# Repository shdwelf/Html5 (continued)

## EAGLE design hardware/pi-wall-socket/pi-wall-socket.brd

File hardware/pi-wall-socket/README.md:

# Pi Wall Socket — a Raspberry Pi Zero 2 W carrier with Ethernet and powerline

Generated CAD: `node tools/build-wallplug-eagle.mjs --design=pi-wall-socket --check`
re-derives these files from `tools/pi-socket-model.mjs` and compares.

| file | what it is |
| --- | --- |
| `pi-wall-socket.lbr` | 22 packages, 18 symbols, 23 devicesets |
| `pi-wall-socket.sch` | 1 sheet (520 × 500 mm), 41 instances, 35 nets |
| `pi-wall-socket.brd` | 180 × 120 mm, 2 layers, 45 elements, 175 pads — **unrouted on purpose** |
| `BOM.md` | every reference, package, fit/DNP, zone, note |

## What it is

A carrier board for a **Raspberry Pi Zero 2 W** that is meant to live in a
wall-socket enclosure. It takes L/N/PE from the socket's own terminals, makes
isolated 12 V, then 5 V for the Pi and 3.3 V for everything else, and gives the Pi
the two network paths it does not have: **wired Ethernet** and
**Ethernet-over-powerline**.

```
L ── F1 ──┬── PS1 (MPM-20-12, 12 V) ──┬── U1 LM2576S-5.0 ── 5 V ── Pi header pins 2/4
          │                           └── U2 LM2576S-3.3 ── 3.3 V ─┬── U4 WIZ850io (SPI0)
N ────────┤                                                        └── U3 PLC Stamp mini 2 (SPI1)
          └── U3 pins 16/17 (L), 15 (N)   ← the modem couples onto the mains
PE ─── J1.3 only, never bonded to SELV ground
```

Why a Zero 2 W and not a Pi 4 or a CM4: the Zero 2 W is 65 × 30 mm with four M2.5
holes on 58 × 23 mm centres, so it fits behind a socket faceplate, and it has no
Ethernet — which is exactly the gap this carrier fills. It is a quad Cortex-A53
(RP3A0/BCM2710A1) at 1 GHz with 512 MB, 2.4 GHz Wi-Fi and BT 4.2, drawing about
3 W max. The industrial alternative is a Compute Module 4, which has an Ethernet
PHY on the module (pins 3-12 are `Ethernet_Pair0..3 P/N`) and takes 5 V on six
pins, but needs two 100-way 0.4 mm DF40C-100DS mezzanine connectors; the PIONIX
EVerest Yak is a published CM4 carrier of exactly that kind.

## Design rules

| rule | value | source |
| --- | --- | --- |
| mains ↔ SELV creepage | **8.0 mm** | PLC Stamp mini 2 datasheet rev 13 §8.3 |
| mains ↔ SELV clearance | 6.5 mm | same |
| isolation | 4000 Vac, inside U3 | same |
| Pi 5 V | header pins 2/4, ≈600 mA max | Pi Zero 2 W: ≈3 W at 5 V |
| Pi 3.3 V output | **left open** | pins 1/17 are the Pi's own regulator, ≈50 mA; paralleling it with a 3 A rail would be a mistake |

`--check` reports the worst mains↔SELV pair as **U3.15 ↔ U3.13 = 13.12 mm** — the
modem's own N pad against its own ZC_IN pad.

## Power budget

| rail | source | loads | margin |
| --- | --- | --- | --- |
| 12 V | MPM-20-12, 20 W | 5 V buck input 391 mA + 3.3 V buck input 206 mA = 597 mA | 64 % |
| 5 V | LM2576S-5.0, 3 A | Pi Zero 2 W 600 mA | 80 % |
| 3.3 V | LM2576S-3.3, 3 A | U3 300 mA (§8.2 max) + U4 180 mA + LEDs/straps/breakout 80 mA = 560 mA | 81 % |

Two buck regulators rather than one: the Pi wants 5 V and the modem wants 3.3 V at
up to 300 mA, and an LDO from 5 V at that current is 0.85 W of heat in a SOT-223.

## The Pi interface

J2 is the Raspberry Pi Zero footprint itself — 40 header pads plus the four Ø2.75
holes in their real relative positions (58 × 23 mm centres, 65 × 30 mm outline) —
so the Pi bolts down onto 2.54 mm female headers with no separate hole parts.

| function | header pins | GPIO |
| --- | --- | --- |
| SPI0 → WIZ850io | 19 MOSI, 21 MISO, 23 SCLK, 24 CE0 | GPIO10/9/11/8 |
| SPI1 → PLC modem | 35 MISO, 38 MOSI, 40 SCLK, 36 CE0 | GPIO19/20/21/16 |
| PLC interrupt / reset | 37 / 31 | GPIO26 / GPIO6 (+ TP6) |
| Ethernet interrupt / reset | 22 / 13 | GPIO25 / GPIO27 (R8 10 kΩ pull-up) |
| UART0 console | 8 TXD, 10 RXD | GPIO14/15, broken out on J3 |
| 5 V in | 2, 4 | from U1 |
| 8 × GND | 6, 9, 14, 20, 25, 30, 34, 39 | |
| spare | 3, 5, 11, 12, 16, 18, 26, 27, 28, 29, 32, 33 | listed in `UNCONNECTED` |

Raspberry Pi OS needs `dtoverlay=spi1-3cs` for the second SPI bus. The Green PHY
side needs Qualcomm's `open-plc-utils` (or chargebyte's V2G Core) and the QCA7000
SPI protocol from chargebyte's AN4; the wired side is a `w5500` SPI device on
`spidev0.0`.

## The socket-outlet relay: considered, and not fitted

A relay-switched outlet was the obvious next block and it is deliberately absent.
The Panasonic **AHES4291** used on the PIONIX EVerest devboard has published pin
roles (1 COM_1, 2 COM_2, 3 COM_3, 4 COIL_1, 5 COIL_2, 6 NC_3, 7 NO_2, 8 NO_1), but
its footprint puts contact pad 3 at (11.45, −16.75) and coil pad 4 at
(3.8, −16.75): **7.65 mm centre-to-centre, ≈4.8 mm between pad edges** — inside
the 8 mm creepage this board keeps for the powerline module. `tests/23-variants.mjs`
measures both numbers so the claim cannot rot.

The Omron **G5LE-1** footprint in the KiCad official library has one pad row at
y = 0/−2 and the other at y = −14.2, i.e. 12.2–15.4 mm between rows, which clears
the rule — but KiCad's symbol leaves the pin names empty (coil and contacts are
separate units), so read the Omron datasheet for which pad is coil+ before routing.
Both footprints are imported and available; see `tools/replacement-parts.mjs`.

Metering is likewise documented rather than fitted: the PIONIX library publishes
the ADE7932ARIZ / ADE7978ACPZ / ADE9078ACPZ energy-metering parts and the
Vacuumschmelze T60404-N4641-X920 current sensor, all imported here.

## Bring-up

1. Power up with no Pi: 12 V at TP1, 5 V at TP4, 3.3 V at TP5.
2. Fit the Pi on 2.54 mm female headers, M2.5 standoffs through the four Ø2.75
   holes. Its own power LED should light from the header 5 V pins.
3. `dtoverlay=spi1-3cs` in `/boot/config.txt`, then check both SPI buses appear.
4. Wired side first: the W5500 driver binds to `spidev0.0`, and link/activity are
   on the module's own RJ45 LEDs.
5. Powerline side: GPIO_0 (LED2) lights when the modem has joined a Green PHY
   network; SW3 held 0.5–3 s starts Simple Connect and LED3 blinks at 1 Hz while
   pairing (datasheet table 5).
6. Console on J3 (UART0, 115200 8N1) — a socket box has no display.

## Safety

* U3 pins 15/16/17 are at mains potential; the module provides 4000 Vac isolation
  with 8 mm creepage / 6.5 mm clearance, and the board keeps 8.0 mm with a
  silkscreen keep-out around those three pads.
* Fit the **CE Class B / North America** variant (`I2PLCBMN-ISC-004-*`) with the
  1:4:5 transformer and on-module zero-cross, pin 13 floating. The automotive
  EVSE/PEV variants are explicitly not for mains (datasheet §12.2).
* PS1 (MPM-20-12) provides the primary isolation; 12 V, 5 V and 3.3 V are SELV.
* F1 is in the line conductor only, MOV1 after it, PE on J1.3 and never bonded to
  SELV ground.
* Both the Pi and the modem have radios, and the modem has a mains coupling: a
  metal faceplate over either changes the result. The silkscreen marks the Pi's
  antenna keep-clear line and the modem's mains keep-out.
* Not certified. A board that lives in a wall-socket enclosure needs IEC/EN 62368-1
  assessment, and the enclosure must keep the socket's live parts further from the
  SELV side than this board alone does.

## Footprint provenance

| package | source |
| --- | --- |
| `PIZERO` | `github.com/tylercrumpton/CrumpPrints.pretty` → `Raspberry_Pi_Zero.kicad_mod`; hole pattern cross-checked against the Raspberry Pi Zero mechanical drawing (65 × 30 mm, four M2.5 holes, 58 × 23 mm centres) |
| `PLCSTAMP` | PIONIX EVerest library; outline and missing pad 14 per chargebyte datasheet §11 |
| `WIZ850IO` | `github.com/es-ude/kicad-library`; pinout from the WIZnet WIZ850io datasheet v1.0 |
| `MPM2012`, `CUI_TB003` | PIONIX EVerest library |
| `LM2576S`, `LRAD12`, `R0603`, `C0603` | KiCad official library |

## Not done

* No routing, and no enclosure. 180 × 120 mm is a wall-mounted enclosure beside or
  behind the socket, not a socket box: a UK single-gang box is 86 × 86 mm.
* No relay, no metering (both documented above with real parts).
* The Pi's mini-HDMI, camera, USB OTG and microSD are on the module and are not
  broken out; a socket-box product provisions over UART0 or Wi-Fi.

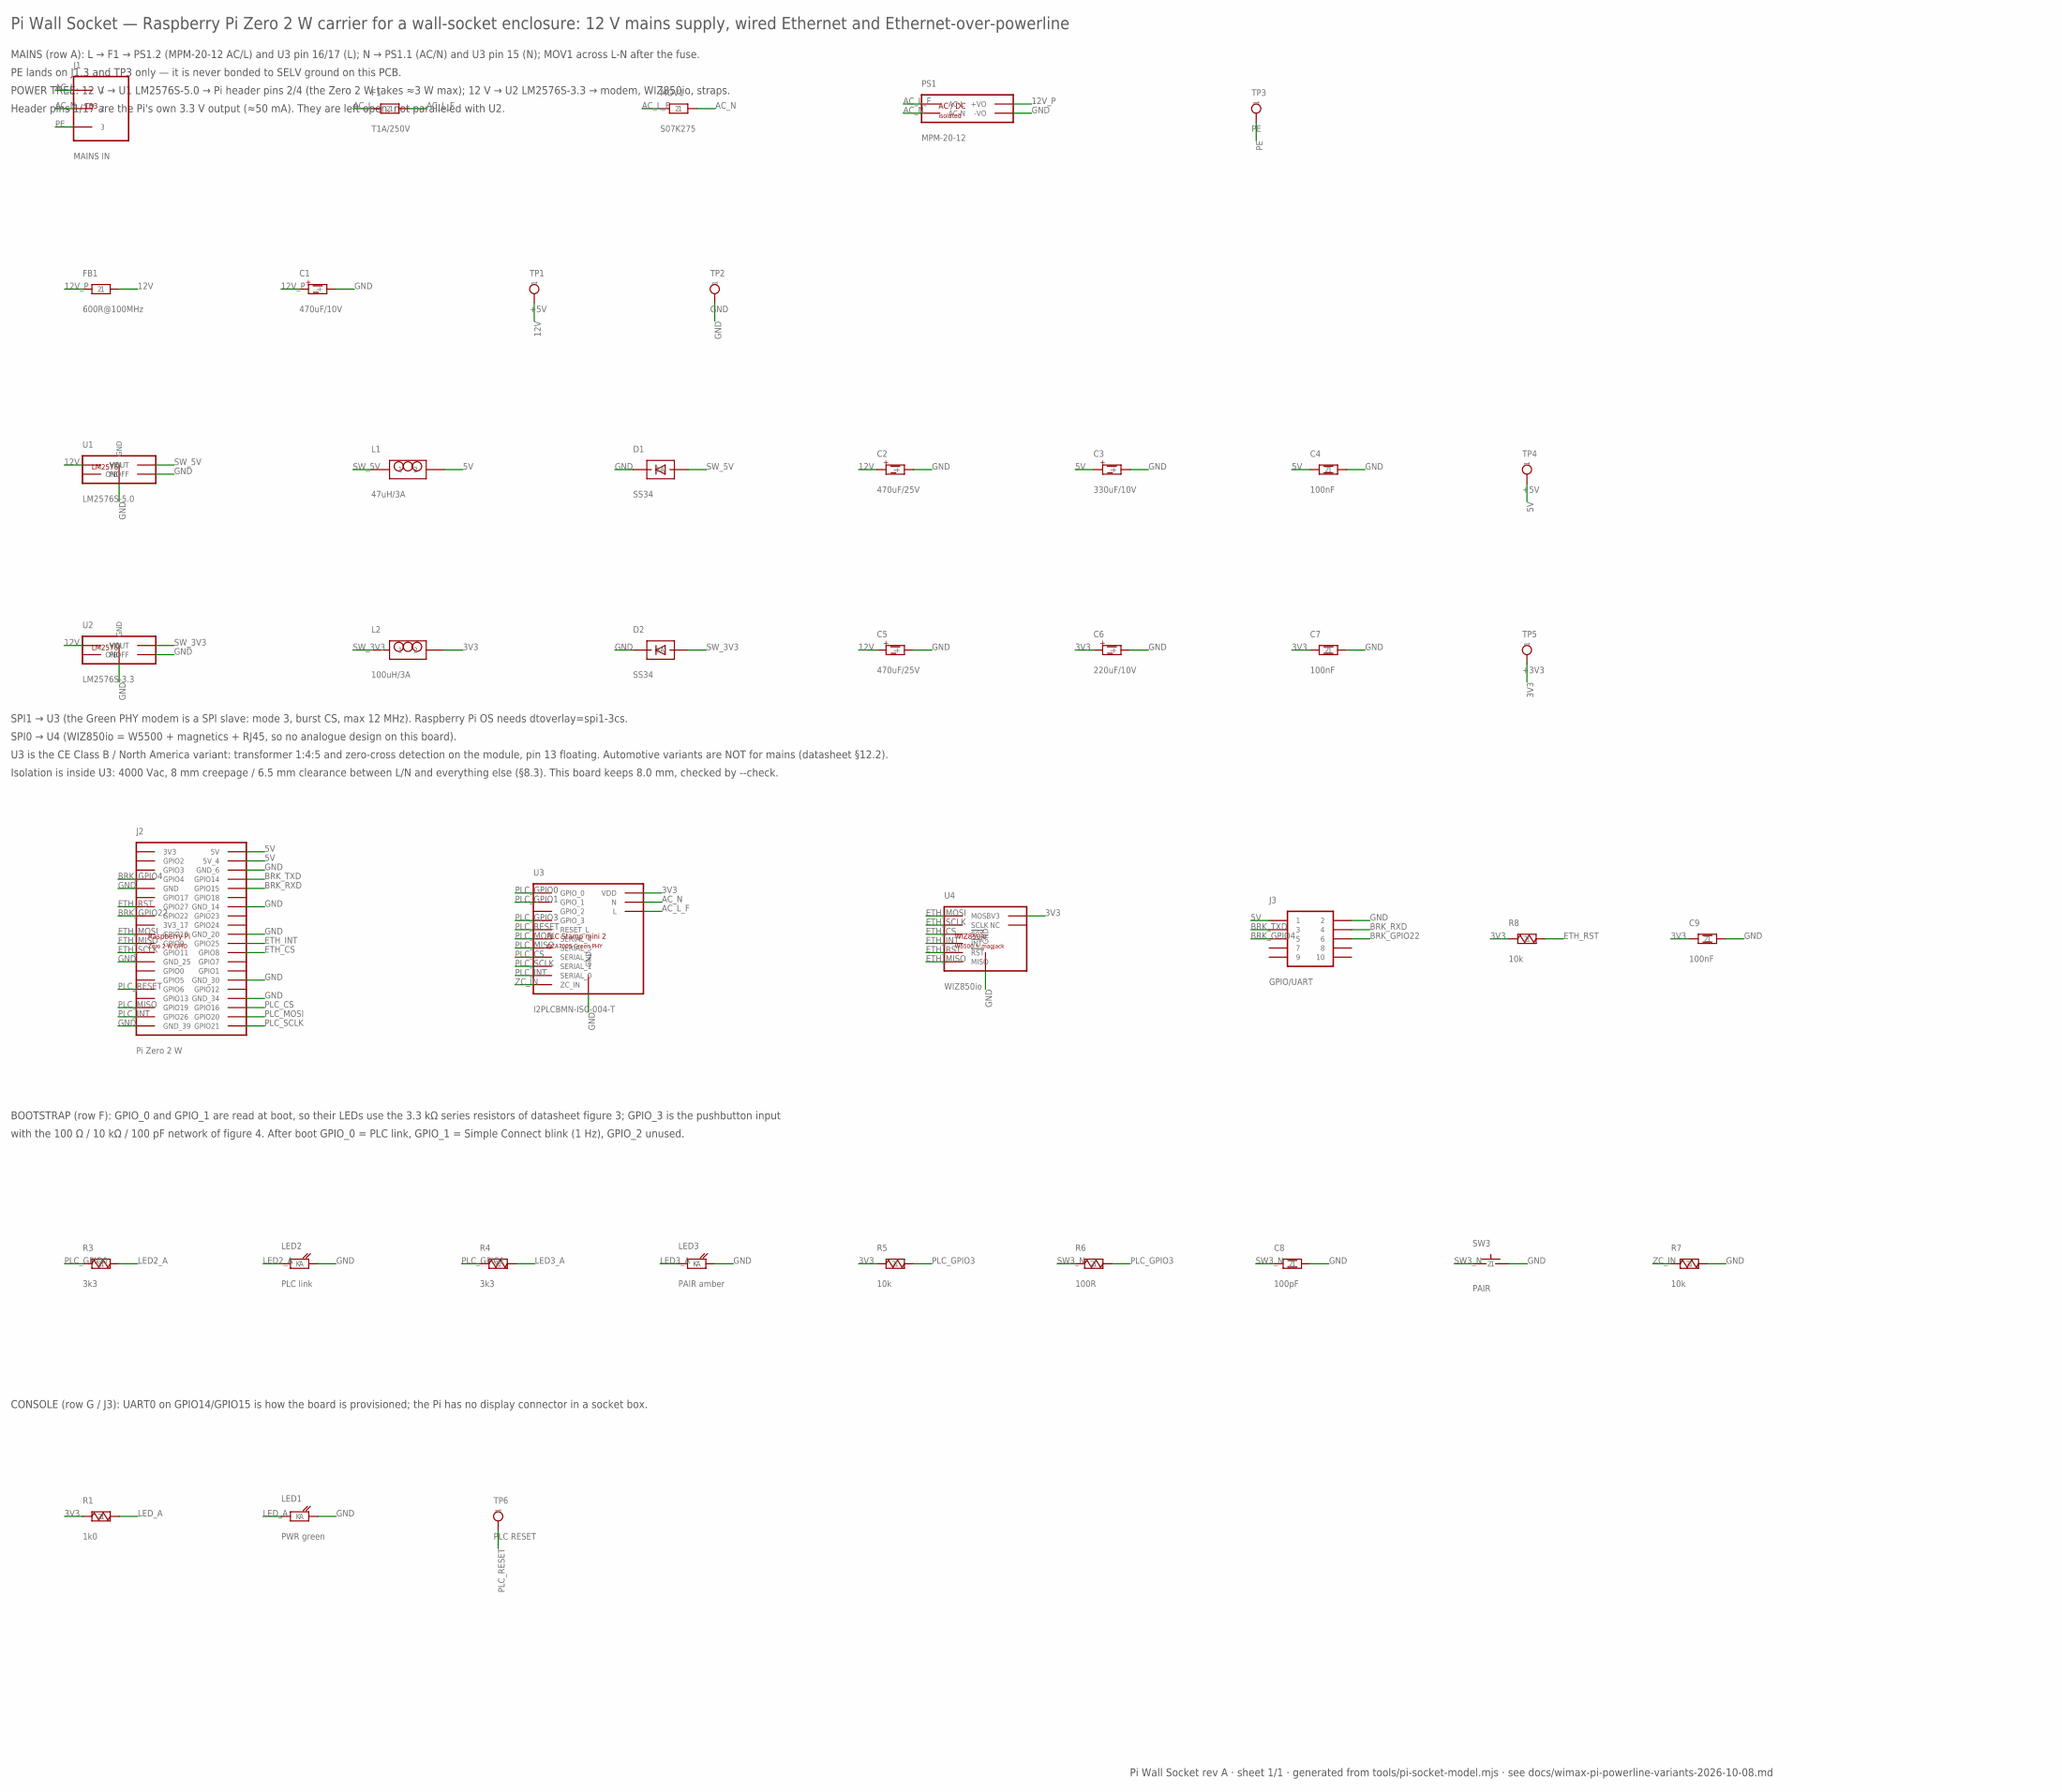
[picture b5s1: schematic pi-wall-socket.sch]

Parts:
C1: 470uF/10V; CP-D10-P5
C2, C5: 470uF/25V; CP-D10-P5
C3: 330uF/10V; CP-D10-P5
C4, C7, C9: 100nF; C0603
C6: 220uF/10V; CP-D10-P5
C8: 100pF; C-5.08
D1, D2: SS34; DO41
F1: T1A/250V; FUSE-RADIAL
FB1: 600R@100MHz; FB-7.62
J1: MAINS IN; CUI_TB003
J2: Pi Zero 2 W; PIZERO
J3: GPIO/UART; HDR-2X5
L1: 47uH/3A; LRAD12
L2: 100uH/3A; LRAD12
LED1: PWR green; LED-5MM
LED2: PLC link; LED-5MM
LED3: PAIR amber; LED-5MM
MOV1: S07K275; MOV07
PS1: MPM-20-12; MPM2012
R1: 1k0; R-7.62
R3, R4: 3k3; R-7.62
R5, R7, R8: 10k; R-7.62
R6: 100R; R-7.62
SW3: PAIR; SW-TACT-6MM
TP1, TP4: +5V; TP
TP2: GND; TP
TP3: PE; TP
TP5: +3V3; TP
TP6: PLC RESET; TP
U1: LM2576S-5.0; LM2576S
U2: LM2576S-3.3; LM2576S
U3: I2PLCBMN-ISC-004-T; PLCSTAMP
U4: WIZ850io; WIZ850IO

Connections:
3V3: C6.+, C7.1, C9.1, L2.2, R1.1, R5.1, R8.1, TP5.1, U3.12 (VDD), U4.8 (3V3), U4.9 (3V3)
5V: C3.+, C4.1, J2.2 (5V), J2.4 (5V_4), J3.1, L1.2, TP4.1
12V: C2.+, C5.+, FB1.2, TP1.1, U1.1 (VIN), U2.1 (VIN)
12V_P: C1.+, FB1.1, PS1.3 (+VO)
AC_L: F1.1, J1.1
AC_L_F: F1.2, MOV1.1, PS1.2 (AC-L), U3.16 (L), U3.17 (L)
AC_N: J1.2, MOV1.2, PS1.1 (AC-N), U3.15 (N)
BRK_GPIO4: J2.7 (GPIO4), J3.5
BRK_GPIO22: J2.15 (GPIO22), J3.6
BRK_RXD: J2.10 (GPIO15), J3.4
BRK_TXD: J2.8 (GPIO14), J3.3
ETH_CS: J2.24 (GPIO8), U4.5 (!SCS)
ETH_INT: J2.22 (GPIO25), U4.6 (!INT)
ETH_MISO: J2.21 (GPIO9), U4.12 (MISO)
ETH_MOSI: J2.19 (GPIO10), U4.3 (MOSI)
ETH_RST: J2.13 (GPIO27), R8.2, U4.11 (!RST)
ETH_SCLK: J2.23 (GPIO11), U4.4 (SCLK)
GND: C1.-, C2.-, C3.-, C4.2, C5.-, C6.-, C7.2, C8.2, C9.2, D1.A, D2.A, J2.6 (GND_6), J2.9 (GND), J2.14 (GND_14), J2.20 (GND_20), J2.25 (GND_25), J2.30 (GND_30), J2.34 (GND_34), J2.39 (GND_39), J3.2, LED1.2 (K), LED2.2 (K), LED3.2 (K), PS1.4 (-VO), R7.2, SW3.2, TP2.1, U1.3 (GND), U1.3_2 (GND), U1.5 (ONOFF), U1.P7 (GND), U1.P8 (GND), U1.P9 (GND), U1.P10 (GND), U2.3 (GND), U2.3_2 (GND), U2.5 (ONOFF), U2.P7 (GND), U2.P8 (GND), U2.P9 (GND), U2.P10 (GND), U3.11 (GND), U3.18 (GND), U3.19 (GND), U3.20 (GND), U3.21 (GND), U3.22 (GND), U3.23 (GND), U3.24 (GND), U3.25 (GND), U4.1 (GND), U4.2 (GND), U4.7 (GND)
LED2_A: LED2.1 (A), R3.2
LED3_A: LED3.1 (A), R4.2
LED_A: LED1.1 (A), R1.2
PE: J1.3, TP3.1
PLC_CS: J2.36 (GPIO16), U3.8 (SERIAL_2)
PLC_GPIO0: R3.1, U3.1 (GPIO_0)
PLC_GPIO1: R4.1, U3.2 (GPIO_1)
PLC_GPIO3: R5.2, R6.2, U3.4 (GPIO_3)
PLC_INT: J2.37 (GPIO26), U3.10 (SERIAL_0)
PLC_MISO: J2.35 (GPIO19), U3.7 (SERIAL_3)
PLC_MOSI: J2.38 (GPIO20), U3.6 (SERIAL_4)
PLC_RESET: J2.31 (GPIO6), TP6.1, U3.5 (RESET_L)
PLC_SCLK: J2.40 (GPIO21), U3.9 (SERIAL_1)
SW3_N: C8.1, R6.1, SW3.1
SW_3V3: D2.K, L2.1, U2.2 (VOUT)
SW_5V: D1.K, L1.1, U1.2 (VOUT)
ZC_IN: R7.1, U3.13 (ZC_IN)

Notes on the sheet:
Pi Wall Socket — Raspberry Pi Zero 2 W carrier for a wall-socket enclosure: 12 V mains supply, wired Ethernet and Ethernet-over-powerline
MAINS (row A): L → F1 → PS1.2 (MPM-20-12 AC/L) and U3 pin 16/17 (L); N → PS1.1 (AC/N) and U3 pin 15 (N); MOV1 across L-N after the fuse.
PE lands on J1.3 and TP3 only — it is never bonded to SELV ground on this PCB.
POWER TREE: 12 V → U1 LM2576S-5.0 → Pi header pins 2/4 (the Zero 2 W takes ≈3 W max); 12 V → U2 LM2576S-3.3 → modem, WIZ850io, straps.
Header pins 1/17 are the Pi's own 3.3 V output (≈50 mA). They are left open, not paralleled with U2.
SPI1 → U3 (the Green PHY modem is a SPI slave: mode 3, burst CS, max 12 MHz). Raspberry Pi OS needs dtoverlay=spi1-3cs.
SPI0 → U4 (WIZ850io = W5500 + magnetics + RJ45, so no analogue design on this board).
U3 is the CE Class B / North America variant: transformer 1:4:5 and zero-cross detection on the module, pin 13 floating. Automotive variants are NOT for mains (datasheet §12.2).
Isolation is inside U3: 4000 Vac, 8 mm creepage / 6.5 mm clearance between L/N and everything else (§8.3). This board keeps 8.0 mm, checked by --check.
BOOTSTRAP (row F): GPIO_0 and GPIO_1 are read at boot, so their LEDs use the 3.3 kΩ series resistors of datasheet figure 3; GPIO_3 is the pushbutton input
with the 100 Ω / 10 kΩ / 100 pF network of figure 4. After boot GPIO_0 = PLC link, GPIO_1 = Simple Connect blink (1 Hz), GPIO_2 unused.
CONSOLE (row G / J3): UART0 on GPIO14/GPIO15 is how the board is provisioned; the Pi has no display connector in a socket box.
Pi Wall Socket rev A · sheet 1/1 · generated from tools/pi-socket-model.mjs · see docs/wimax-pi-powerline-variants-2026-10-08.md

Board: 2 copper layers, 45 parts (0 on the bottom side), 35 nets, no tracks yet.

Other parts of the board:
H1, H2, H3, H4: MOUNT-M3

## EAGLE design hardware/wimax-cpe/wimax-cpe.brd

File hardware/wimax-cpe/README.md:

# WiMAX CPE Wallplug — a mains-powered Mini Card carrier

Generated CAD: `node tools/build-wallplug-eagle.mjs --design=wimax-cpe --check`
re-derives these files from `tools/wimax-cpe-model.mjs` and compares.

| file | what it is |
| --- | --- |
| `wimax-cpe.lbr` | 22 packages, 18 symbols, 21 devicesets |
| `wimax-cpe.sch` | 1 sheet, 40 instances, 25 nets |
| `wimax-cpe.brd` | 140 × 90 mm, 2 layers, 44 elements, 160 pads — **unrouted on purpose** |
| `BOM.md` | every reference, package, fit/DNP, zone, note |

## What it is, and what it is not

A wallplug that powers a **PCI Express Mini Card** WiMAX modem and connects it to a
host over **USB 2.0**. The reference card is an Intel Centrino Advanced-N +
WiMAX 6250 (622ANXHMW): IEEE 802.16e-2005 Wave 2, Mobile WiMAX Release 1 Wave 2
system profile, 2.3 / 2.5 / 3.5 GHz, 20 Mbps down / 6 Mbps up over WiMAX, half
Mini Card 26.65 × 29.85 × 4.39 mm, 4.5 g, 3.3 V, two U.FL antenna jacks.

The honest limitation is in Intel's own product brief: **"Connector interface: PCIe
electrical interface for Wi-Fi, USB 2.0 for WiMAX."** A wallplug has no PCIe root
complex, so this carrier wires the USB half to an upstream micro-USB receptacle and
leaves `REFCLK±`, `PERn0/PERp0`, `PETp0` and `CLKREQ#` open. On this board the
802.11 radio stays dark and the 802.16e radio is the product. `LED_WLAN#` still
drives LED3, which will simply never light.

And the second honest limitation: **there are no WiMAX networks left.** Sprint and
Clearwater shut their 802.16e service down in 2015-2016. This board is therefore a
carrier for surplus cards, a teaching artefact, or — with J4 and U3 fitted — an LTE
mini-PCIe board, which is what `tools/replacement-parts.mjs` recommends.

```
L ── F1 ──┬── PS1 (MPM-20-12, isolated 12 V) ── FB1 ── U1 (LM2576S-3.3) ── 3V3 ──┐
N ────────┘                                                                       │
                                     U2 = mini-PCIe socket, five 3.3 Vaux pins ───┘
                                     J3 = micro-USB upstream: D+/D- to socket 38/36
                                     J4 = micro-SIM (DNP) on UIM_PWR/DATA/CLK/RESET
```

## Design rules

| rule | value | source |
| --- | --- | --- |
| mains ↔ SELV creepage | 6.4 mm | IEC 60664-1 / 62368-1 reinforced insulation at 250 V rms; no powerline module on this board, so the module-specific 8 mm figure does not apply |
| mains ↔ SELV clearance | 4.0 mm | same |
| 3.3 V rail | 3 A buck, five socket contacts | Mini Card EM spec rev 1.2: "Current Rating 0.50 A/power contact (continuous)" |
| card budget | 1100 mA at 3.3 V | PEAK Systems PCIe-miniPCIe adapter manual: 3.3 V max 1100 mA, 1.5 V max 375 mA |

`--check` reports the worst mains↔SELV pair as **TP3.1 ↔ TP8.1 = 16.03 mm**.

## Power budget

| rail | source | loads | margin |
| --- | --- | --- | --- |
| 12 V | MPM-20-12, 20 W / 1.67 A | U1 buck input ≈ 447 mA | 73 % |
| 3.3 V | LM2576S-3.3, 3 A | card 1100 mA + LEDs/pull-ups 30 mA | 62 % |

## The socket, pin by pin

52 positions, 0.8 mm pitch, two staggered rows (0.4 mm offset), two Ø2.6
non-plated mounting holes 24.2 mm apart. Signal names follow the PCI Express Mini
Card Electromechanical Specification rev 1.2, cross-checked against
hardwarebook.info and ARM's DSTREAM documentation (they agree).

| pins | what this board does |
| --- | --- |
| 2, 24, 39, 41, 52 (+3.3 Vaux) | all five tied to the 3.3 V rail, each decoupled locally by C5/C6/C7 |
| 4, 9, 15, 18, 21, 26, 27, 29, 31, 34, 35, 37, 40, 50 (GND) | ground |
| 36, 38 (USB_D−/D+) | to J3 (micro-USB upstream) and to TP7/TP8 |
| 22 (PERST#) | 10 kΩ pull-up R2: no PCIe host, so the card is held out of reset |
| 20, 51 (W_DISABLE#, W_DISABLE2#) | 10 kΩ pull-up R3 + SW4 to ground — the radio-disable the EM spec §3.2.5.2 requires a system to provide |
| 30, 32 (SMB_CLK, SMB_DATA) | 2.2 kΩ pull-ups R4/R5 |
| 42, 43 (LED_WWAN#, LED_WLAN#) | open-drain LED drives through 3.3 kΩ R6/R7 |
| 8, 10, 12, 14 (UIM_PWR, UIM_DATA, UIM_CLK, UIM_RESET) | to J4 micro-SIM (**DNP**: the Intel 6250 has no SIM; an LTE swap-in does) |
| 6, 28, 48 (+1.5 V) | from U3 AMS1117-1.5 (**DNP** — the 6250 is 3.3 V only) |
| 16 (UIM_VPP), 17, 19, 44, 45, 46, 47, 49 | open, each listed in `UNCONNECTED` with a reason |
| 1 (WAKE#), 3/5 (COEX1/2), 7 (CLKREQ#), 11/13 (REFCLK±), 23/25/33 (PCIe pairs) | open: coexistence and PCIe are laptop-host features this carrier does not have |

## Antennas are enclosure items, not board parts

The card carries its own **Hirose U.FL-R-SMT** jacks, which mate with **U.FL-LP-066**
cable connectors (Intel's WiFi Adapter Information Guide names both). So the
carrier board has no RF path to feed: the enclosure takes two U.FL → SMA bulkhead
pigtails and two antennas for the card's band. The silkscreen draws the card
outline (30 × 26.8 mm from the socket) and an RF keep-out over its antenna end;
`BOARD_LINES` in the model is where that drawing lives, and the imported `UFL`,
`SMAV` and `UMTSANT` footprints are available for a board that does need them.

## Bring-up

1. Check 12 V at TP1 and 3.3 V at TP4 before fitting the card.
2. Fit the card, then check 3.3 Vaux at TP5 with the card in circuit — a card that
   drags the rail below 3.15 V is drawing more than this budget allows.
3. Connect J3 to a host (a PC, or a Raspberry Pi's OTG port). The host must
   enumerate a USB device; on Linux the 6250's WiMAX side wants the `i2400m_usb`
   driver and a `wimaxd`-class daemon, both of which are historical now.
4. SW4 must be released (high) for the radio to be enabled.

## Safety

* F1 is in the line conductor only; MOV1 is after the fuse. PE lands on J1.3 and
  TP3 and is not bonded to SELV ground.
* PS1 (MEAN WELL MPM-20-12) provides the isolation; the PCB keeps 6.4 mm creepage
  and 4.0 mm clearance, enforced by `--check`.
* A transmitter has regulatory consequences beyond safety: W_DISABLE# must be
  reachable (SW4), and the antenna keep-out is part of the RF design, not
  decoration. The card's own FCC/RED certification does not transfer to this
  enclosure automatically.
* Not certified. IEC/EN 62368-1 assessment is needed before this goes anywhere
  near a wall.

## Footprint provenance

| package | source |
| --- | --- |
| `MPCIE` | `github.com/drbild/kicad-mini-pci-e` → `mpcie.pretty/mini-PCIe_H1_Half.kicad_mod`; courtyard set to the 30 × 26.8 mm half-size card area |
| `MPM2012` | `github.com/PionixPublic/reference-hardware` → `Yak/lib/ev-devboard.pretty/MPM2012.kicad_mod`; pin roles from that project's symbol (1 AC/N, 2 AC/L, 3 +V, 4 −V) |
| `USBMB` | KiCad official `Connector_USB/USB_Micro-B_Molex-105017-0001` |
| `MICROSIM` | KiCad official `Connector_Card/microSIM_JAE_SF53S006VCBR2000` |
| `LM2576S`, `AMS1117`, `LRAD12`, `CUI_TB003` | KiCad official / PIONIX libraries |

## Not done

* No routing, no RF work (there is no RF on this board), no PCIe.
* `UIM_VPP` is left open: SIM programming voltage is obsolete in 3G/4G UICCs. If a
  card asks for it, that is a different SIM interface than the one wired here.
* The 1.5 V rail is a DNP option, not a tested path — nothing on the reference card
  uses it, so it has never been loaded.

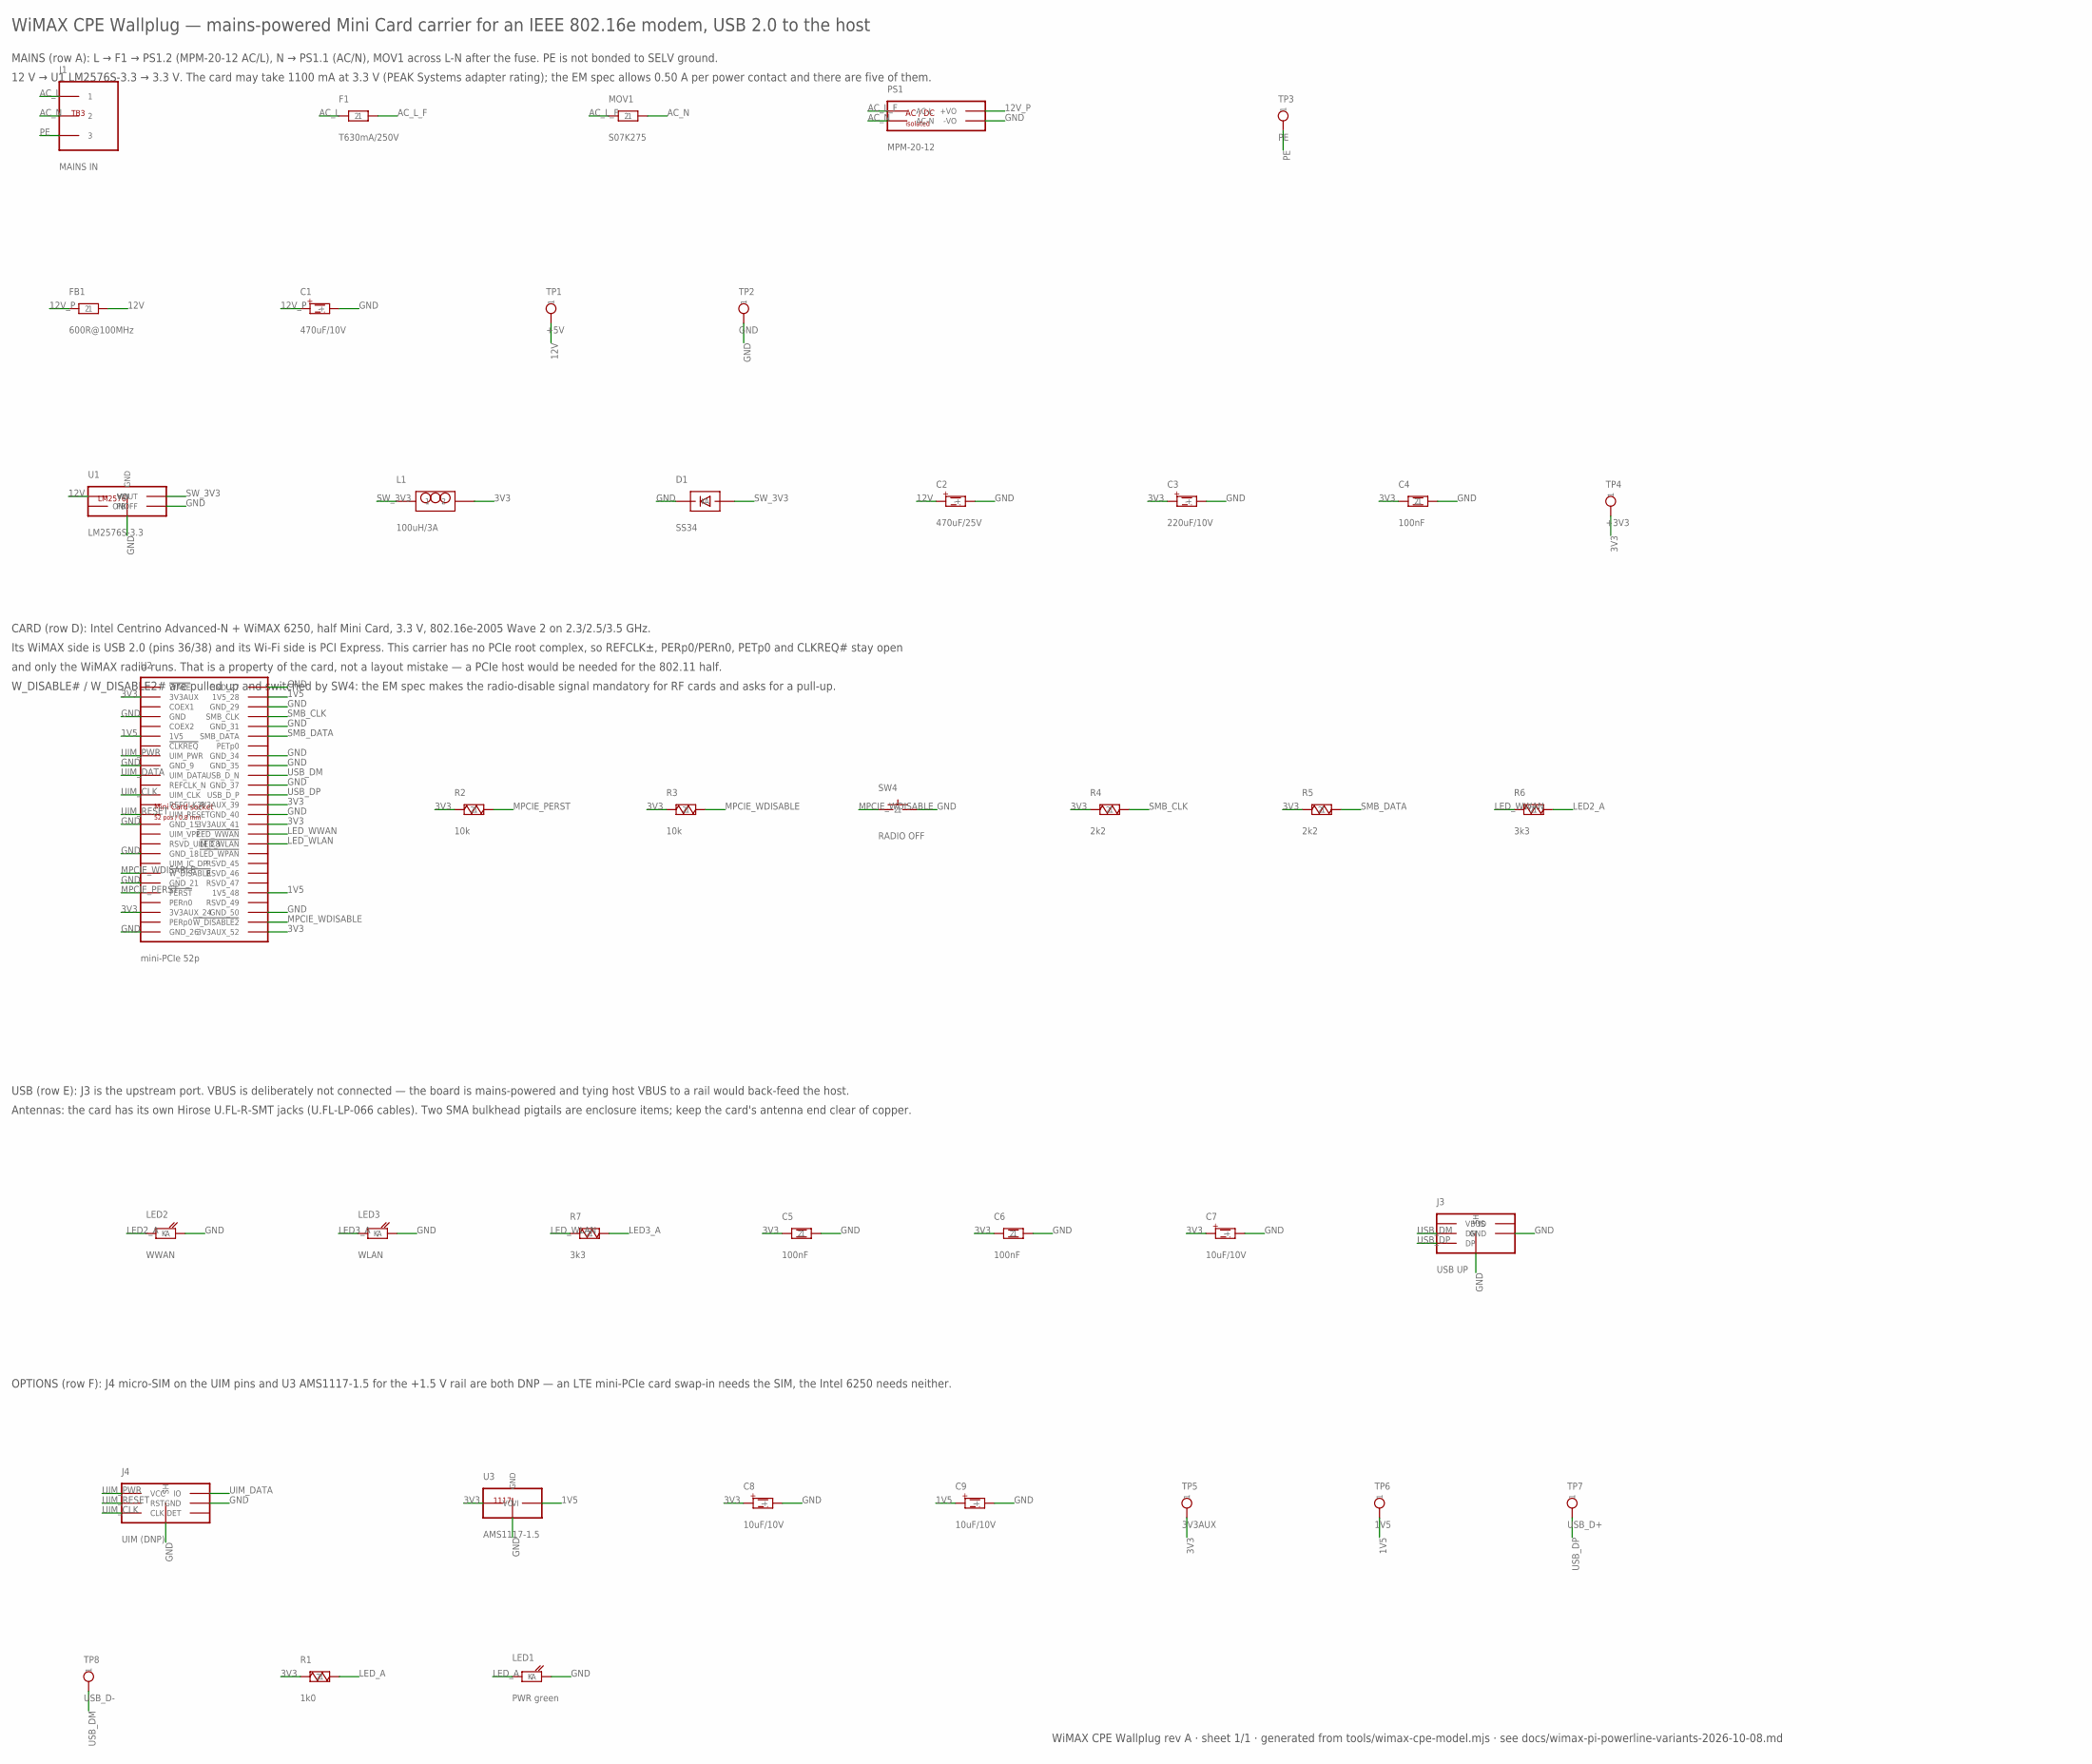
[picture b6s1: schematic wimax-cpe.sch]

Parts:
C1: 470uF/10V; CP-D10-P5
C2: 470uF/25V; CP-D10-P5
C3: 220uF/10V; CP-D10-P5
C4, C5, C6: 100nF; C0603
C7, C8, C9: 10uF/10V; CP-D6.3-P2.5
D1: SS34; DO41
F1: T630mA/250V; FUSE-RADIAL
FB1: 600R@100MHz; FB-7.62
J1: MAINS IN; CUI_TB003
J3: USB UP; USBMB
J4: UIM (DNP); MICROSIM
L1: 100uH/3A; LRAD12
LED1: PWR green; LED-5MM
LED2: WWAN; LED-5MM
LED3: WLAN; LED-5MM
MOV1: S07K275; MOV07
PS1: MPM-20-12; MPM2012
R1: 1k0; R-7.62
R2, R3: 10k; R-7.62
R4, R5: 2k2; R-7.62
R6, R7: 3k3; R-7.62
SW4: RADIO OFF; SW-TACT-6MM
TP1: +5V; TP
TP2: GND; TP
TP3: PE; TP
TP4: +3V3; TP
TP5: 3V3AUX; TP
TP6: 1V5; TP
TP7: USB_D+; TP
TP8: USB_D-; TP
U1: LM2576S-3.3; LM2576S
U2: mini-PCIe 52p; MPCIE
U3: AMS1117-1.5; AMS1117

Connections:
1V5: C9.+, TP6.1, U2.6 (1V5), U2.28 (1V5_28), U2.48 (1V5_48), U3.2 (VO), U3.2_2 (VO)
3V3: C3.+, C4.1, C5.1, C6.1, C7.+, C8.+, L1.2, R1.1, R2.1, R3.1, R4.1, R5.1, TP4.1, TP5.1, U2.2 (3V3AUX), U2.24 (3V3AUX_24), U2.39 (3V3AUX_39), U2.41 (3V3AUX_41), U2.52 (3V3AUX_52), U3.3 (VI)
12V: C2.+, FB1.2, TP1.1, U1.1 (VIN)
12V_P: C1.+, FB1.1, PS1.3 (+VO)
AC_L: F1.1, J1.1
AC_L_F: F1.2, MOV1.1, PS1.2 (AC-L)
AC_N: J1.2, MOV1.2, PS1.1 (AC-N)
GND: C1.-, C2.-, C3.-, C4.2, C5.2, C6.2, C7.-, C8.-, C9.-, D1.A, J3.5 (GND), J3.6 (SH), J3.6_2 (SH), J3.6_3 (SH), J3.6_4 (SH), J3.6_5 (SH), J3.6_6 (SH), J3.6_7 (SH), J3.6_8 (SH), J4.5 (GND), J4.SH, J4.SH_2 (SH), J4.SH_3 (SH), J4.SH_4 (SH), J4.SH_5 (SH), J4.SH_6 (SH), J4.SH_7 (SH), J4.SH_8 (SH), LED1.2 (K), LED2.2 (K), LED3.2 (K), PS1.4 (-VO), SW4.2, TP2.1, U1.3 (GND), U1.3_2 (GND), U1.5 (ONOFF), U1.P7 (GND), U1.P8 (GND), U1.P9 (GND), U1.P10 (GND), U2.4 (GND), U2.9 (GND_9), U2.15 (GND_15), U2.18 (GND_18), U2.21 (GND_21), U2.26 (GND_26), U2.27 (GND_27), U2.29 (GND_29), U2.31 (GND_31), U2.34 (GND_34), U2.35 (GND_35), U2.37 (GND_37), U2.40 (GND_40), U2.50 (GND_50), U3.1 (GND)
LED2_A: LED2.1 (A), R6.2
LED3_A: LED3.1 (A), R7.2
LED_A: LED1.1 (A), R1.2
LED_WLAN: R7.1, U2.43 (!LED_WLAN)
LED_WWAN: R6.1, U2.42 (!LED_WWAN)
MPCIE_PERST: R2.2, U2.22 (!PERST)
MPCIE_WDISABLE: R3.2, SW4.1, U2.20 (!W_DISABLE), U2.51 (!W_DISABLE2)
PE: J1.3, TP3.1
SMB_CLK: R4.2, U2.30 (SMB_CLK)
SMB_DATA: R5.2, U2.32 (SMB_DATA)
SW_3V3: D1.K, L1.1, U1.2 (VOUT)
UIM_CLK: J4.3 (CLK), U2.12 (UIM_CLK)
UIM_DATA: J4.7 (IO), U2.10 (UIM_DATA)
UIM_PWR: J4.1 (VCC), U2.8 (UIM_PWR)
UIM_RESET: J4.2 (RST), U2.14 (UIM_RESET)
USB_DM: J3.2 (DM), TP8.1, U2.36 (USB_D_N)
USB_DP: J3.3 (DP), TP7.1, U2.38 (USB_D_P)

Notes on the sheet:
WiMAX CPE Wallplug — mains-powered Mini Card carrier for an IEEE 802.16e modem, USB 2.0 to the host
MAINS (row A): L → F1 → PS1.2 (MPM-20-12 AC/L), N → PS1.1 (AC/N), MOV1 across L-N after the fuse. PE is not bonded to SELV ground.
12 V → U1 LM2576S-3.3 → 3.3 V. The card may take 1100 mA at 3.3 V (PEAK Systems adapter rating); the EM spec allows 0.50 A per power contact and there are five of them.
CARD (row D): Intel Centrino Advanced-N + WiMAX 6250, half Mini Card, 3.3 V, 802.16e-2005 Wave 2 on 2.3/2.5/3.5 GHz.
Its WiMAX side is USB 2.0 (pins 36/38) and its Wi-Fi side is PCI Express. This carrier has no PCIe root complex, so REFCLK±, PERp0/PERn0, PETp0 and CLKREQ# stay open
and only the WiMAX radio runs. That is a property of the card, not a layout mistake — a PCIe host would be needed for the 802.11 half.
W_DISABLE# / W_DISABLE2# are pulled up and switched by SW4: the EM spec makes the radio-disable signal mandatory for RF cards and asks for a pull-up.
USB (row E): J3 is the upstream port. VBUS is deliberately not connected — the board is mains-powered and tying host VBUS to a rail would back-feed the host.
Antennas: the card has its own Hirose U.FL-R-SMT jacks (U.FL-LP-066 cables). Two SMA bulkhead pigtails are enclosure items; keep the card's antenna end clear of copper.
OPTIONS (row F): J4 micro-SIM on the UIM pins and U3 AMS1117-1.5 for the +1.5 V rail are both DNP — an LTE mini-PCIe card swap-in needs the SIM, the Intel 6250 needs neither.
WiMAX CPE Wallplug rev A · sheet 1/1 · generated from tools/wimax-cpe-model.mjs · see docs/wimax-pi-powerline-variants-2026-10-08.md

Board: 2 copper layers, 44 parts (0 on the bottom side), 25 nets, no tracks yet.

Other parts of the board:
H1, H2, H3, H4: MOUNT-M3
